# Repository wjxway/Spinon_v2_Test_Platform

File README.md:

# Maneuverable Piccolissimo 4 (MP4) Test Platform Setup Guide

Maneuverable Piccolissimo 4 test platform, or MP4 test platform for short, is a single motor drone system designed to test the dynamics of the drone before we build the full distributed version of MP4 system. Instead of using peer-to-peer communication between drones to achieve control like it will be in the MP4 system, this test platform uses external optical tracking system like Optitrack to obtain high accuracy drone position, making it easier to test subsystems like aerodynamics or control.

For more details of this system, please check (and cite!) our paper at [RSS proceedings website](https://www.roboticsproceedings.org/rss20/p102.html). For assembly guide, please visit [this document](https://1drv.ms/w/s!Aq5Al0CEiWQnkfE0qJTTQATZVnzniQ).

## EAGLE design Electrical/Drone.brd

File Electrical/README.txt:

CAM_Files.zip contains the CAM files needed to manufacture and assemble the PCB.

In the schematics, I'm using pinhead as power plugs and SSM6K504NU FET instead of the G2014.
When building the board, make sure you do not install the pinhead (use wires with headers instead) and install Goford G2014 FET.

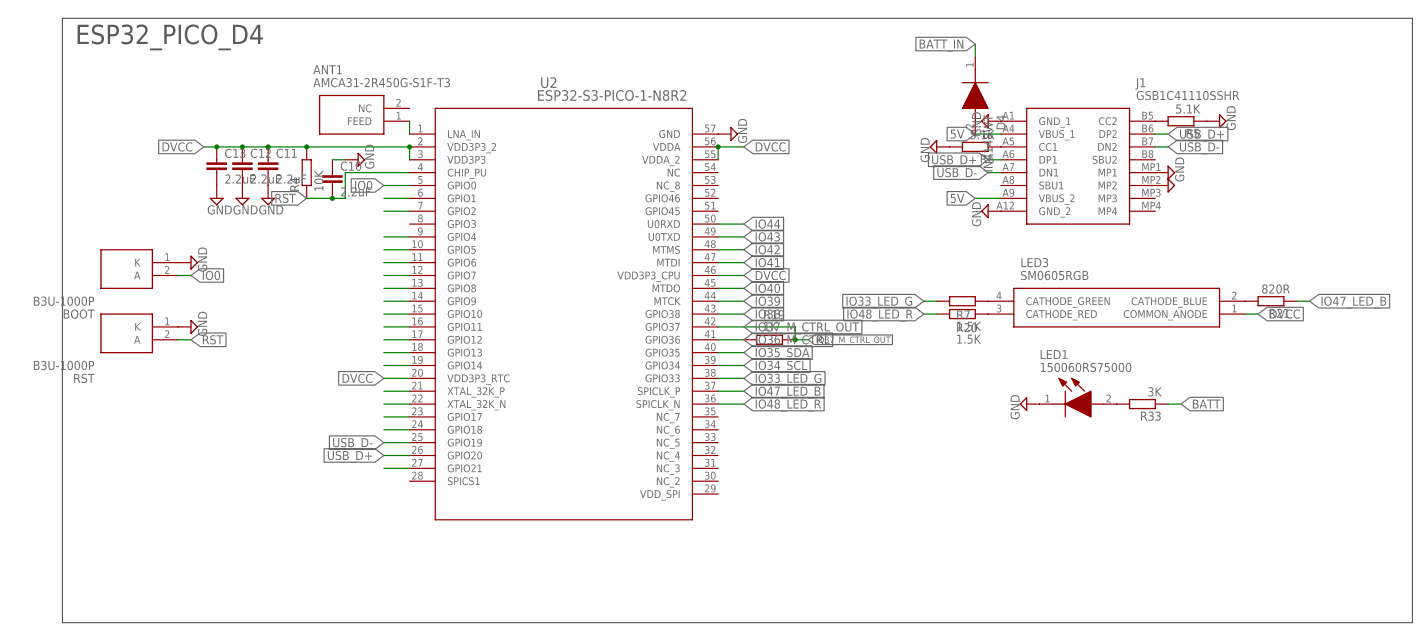
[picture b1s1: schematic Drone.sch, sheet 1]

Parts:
ANT1: AMCA31-2R450G-S1F-T3; ANTC3216X140N
BOOT: B3U-1000P
C10, C11, C12, C13: 2.2uF; C0402_STANDARD
D4: IN4148WT; SODFL1608X70N
J1: GSB1C41110SSHR
LED1: 150060RS75000; LEDC1608X80N
LED3: SM0605RGB
R4: 10K; R0402_STANDARD
R5, R6: 5.1K; R0402_STANDARD
R7, R20: 1.5K; R0402_STANDARD
R19: 1K; R0402_STANDARD
R21: 820R; R0402_STANDARD
R33: 3K; R0402_STANDARD
RST: B3U-1000P
U2: ESP32-S3-PICO-1-N8R2; QFN56_7X7_EXP

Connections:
5V: D4.2 (A), J1.A4 (VBUS_1), J1.A9 (VBUS_2)
BATT: R33.1; also elsewhere on the board
BATT_IN: D4.1 (K); also elsewhere on the board
DVCC: C11.1, C12.1, C13.1, LED3.1 (COMMON_ANODE), R4.2, U2.2 (VDD3P3_2), U2.3 (VDD3P3), U2.20 (VDD3P3_RTC), U2.46 (VDD3P3_CPU), U2.55 (VDDA_2), U2.56 (VDDA); also elsewhere on the board
GND: BOOT.1 (K), C10.1, C11.2, C12.2, C13.2, J1.A1 (GND_1), J1.A12 (GND_2), J1.MP1, J1.MP2, LED1.1 (K), R5.1, R6.2, RST.1 (K), U2.57 (GND); also elsewhere on the board
IO0: BOOT.2 (A), U2.5 (GPIO0)
IO33_LED_G: R7.2, U2.38 (GPIO33)
IO34_SCL: U2.39 (GPIO34); also elsewhere on the board
IO35_SDA: U2.40 (GPIO35); also elsewhere on the board
IO36_M_CTRL: R19.2, U2.41 (GPIO36)
IO37_M_CTRL_OUT: R19.1, U2.42 (GPIO37); also elsewhere on the board
IO38: U2.43 (GPIO38)
IO39: U2.44 (MTCK)
IO40: U2.45 (MTDO)
IO41: U2.47 (MTDI)
IO42: U2.48 (MTMS)
IO43: U2.49 (U0TXD)
IO44: U2.50 (U0RXD)
IO47_LED_B: R21.1, U2.37 (SPICLK_P)
IO48_LED_R: R20.2, U2.36 (SPICLK_N)
unnamed: ANT1.1 (FEED), U2.1 (LNA_IN)
unnamed: LED3.4 (CATHODE_GREEN), R7.1
unnamed: J1.A5 (CC1), R6.1
unnamed: LED1.2 (A), R33.2
unnamed: LED3.2 (CATHODE_BLUE), R21.2
unnamed: J1.B5 (CC2), R5.2
unnamed: LED3.3 (CATHODE_RED), R20.1
RST: C10.2, R4.1, RST.2 (A), U2.4 (CHIP_PU)
USB_D+: J1.A6 (DP1), J1.B6 (DP2), U2.26 (GPIO20)
USB_D-: J1.A7 (DN1), J1.B7 (DN2), U2.25 (GPIO19)
VDD_SPI: U2.29 (VDD_SPI)

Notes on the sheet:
ESP32_PICO_D4

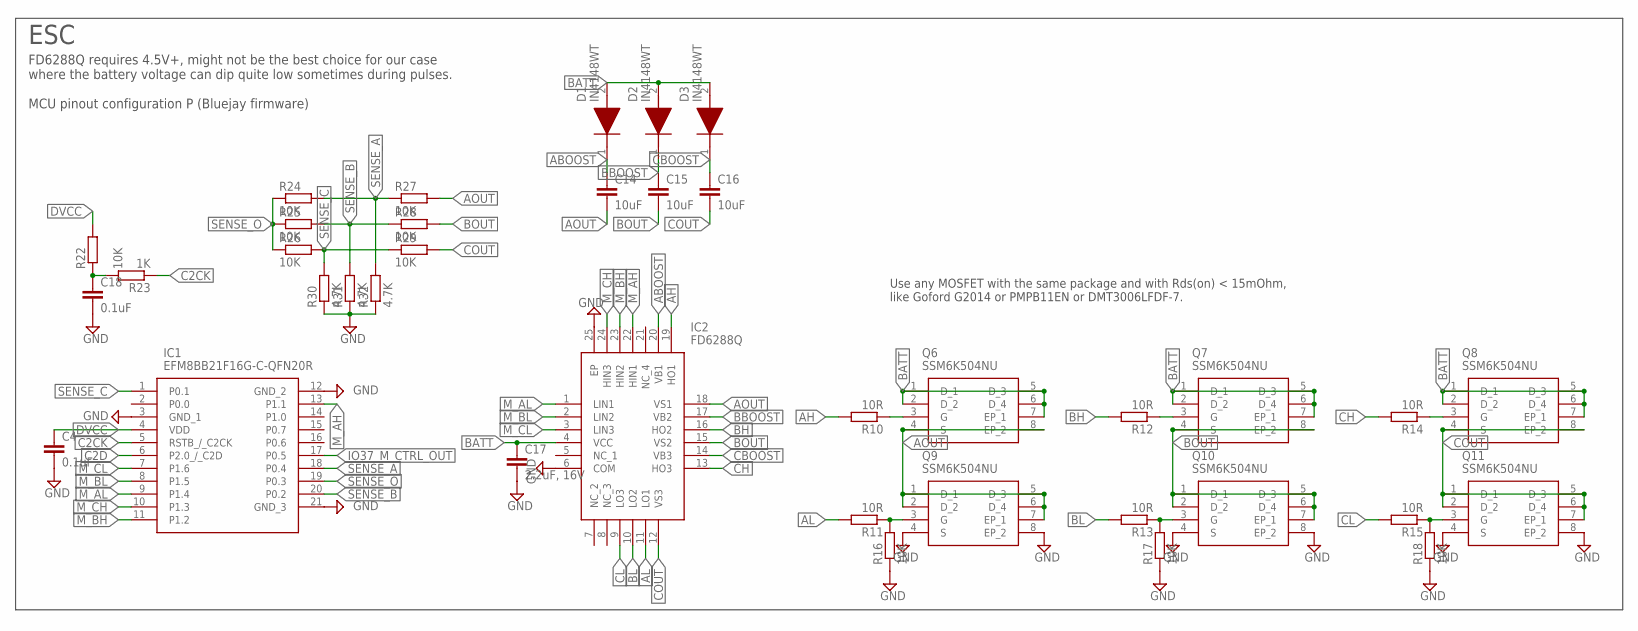
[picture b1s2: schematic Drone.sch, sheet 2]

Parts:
C4, C18: 0.1uF; C0402_STANDARD
C14, C15, C16: 10uF; C0402_STANDARD
C17: 2.2uF, 16V; C0402_STANDARD
D1, D2, D3: IN4148WT; SODFL1608X70N
IC1: EFM8BB21F16G-C-QFN20R; EFM8BB21F16GCQFN20R
IC2: FD6288Q; QFN50P400X400X90-25N
Q6, Q7, Q8, Q9, Q10, Q11: SSM6K504NU
R10, R11, R12, R13, R14, R15: 10R; R0402_STANDARD
R16, R17, R18, R22, R24, R25, R26, R27, R28, R29: 10K; R0402_STANDARD
R23: 1K; R0402_STANDARD
R30, R31, R32: 4.7K; R0402_STANDARD

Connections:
ABOOST: C14.1, D1.1 (K), IC2.20 (VB1)
AH: IC2.19 (HO1), R10.2
AL: IC2.11 (LO1), R11.2
AOUT: C14.2, IC2.18 (VS1), Q6.4 (S), Q6.8 (EP_2), Q9.1 (D_1), Q9.2 (D_2), Q9.5 (D_3), Q9.6 (D_4), Q9.7 (EP_1), R27.2
BATT: C17.1, D1.2 (A), D2.2 (A), D3.2 (A), IC2.4 (VCC), Q6.1 (D_1), Q6.2 (D_2), Q6.5 (D_3), Q6.6 (D_4), Q6.7 (EP_1), Q7.1 (D_1), Q7.2 (D_2), Q7.5 (D_3), Q7.6 (D_4), Q7.7 (EP_1), Q8.1 (D_1), Q8.2 (D_2), Q8.5 (D_3), Q8.6 (D_4), Q8.7 (EP_1); also elsewhere on the board
BBOOST: C15.1, D2.1 (K), IC2.17 (VB2)
BH: IC2.16 (HO2), R12.2
BL: IC2.10 (LO2), R13.2
BOUT: C15.2, IC2.15 (VS2), Q7.4 (S), Q7.8 (EP_2), Q10.1 (D_1), Q10.2 (D_2), Q10.5 (D_3), Q10.6 (D_4), Q10.7 (EP_1), R28.2
C2CK: IC1.5 (RSTB_/_C2CK), R23.1
C2D: IC1.6 (P2.0_/_C2D)
CBOOST: C16.1, D3.1 (K), IC2.14 (VB3)
CH: IC2.13 (HO3), R14.2
CL: IC2.9 (LO3), R15.2
COUT: C16.2, IC2.12 (VS3), Q8.4 (S), Q8.8 (EP_2), Q11.1 (D_1), Q11.2 (D_2), Q11.5 (D_3), Q11.6 (D_4), Q11.7 (EP_1), R29.2
DVCC: C4.1, IC1.4 (VDD), R22.2; also elsewhere on the board
GND: C4.2, C17.2, C18.2, IC1.3 (GND_1), IC1.12 (GND_2), IC1.21 (GND_3), IC2.6 (COM), IC2.25 (EP), Q9.4 (S), Q9.8 (EP_2), Q10.4 (S), Q10.8 (EP_2), Q11.4 (S), Q11.8 (EP_2), R16.1, R17.1, R18.1, R30.1, R31.1, R32.1; also elsewhere on the board
IO37_M_CTRL_OUT: IC1.17 (P0.5); also elsewhere on the board
M_AH: IC1.13 (P1.1), IC2.22 (HIN1)
M_AL: IC1.9 (P1.4), IC2.1 (LIN1)
M_BH: IC1.11 (P1.2), IC2.23 (HIN2)
M_BL: IC1.8 (P1.5), IC2.2 (LIN2)
M_CH: IC1.10 (P1.3), IC2.24 (HIN3)
M_CL: IC1.7 (P1.6), IC2.3 (LIN3)
unnamed: Q6.3 (G), R10.1
unnamed: Q9.3 (G), R11.1, R16.2
unnamed: Q7.3 (G), R12.1
unnamed: Q10.3 (G), R13.1, R17.2
unnamed: Q8.3 (G), R14.1
unnamed: Q11.3 (G), R15.1, R18.2
unnamed: C18.1, R22.1, R23.2
SENSE_A: IC1.18 (P0.4), R24.2, R27.1, R32.2
SENSE_B: IC1.20 (P0.2), R25.2, R28.1, R31.2
SENSE_C: IC1.1 (P0.1), R26.2, R29.1, R30.2
SENSE_O: IC1.19 (P0.3), R24.1, R25.1, R26.1

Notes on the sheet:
ESC
FD6288Q requires 4.5V+, might not be the best choice for our case where the battery voltage can dip quite low sometimes during pulses. MCU pinout configuration P (Bluejay firmware)
Use any MOSFET with the same package and with Rds(on) < 15mOhm, like Goford G2014 or PMPB11EN or DMT3006LFDF-7.

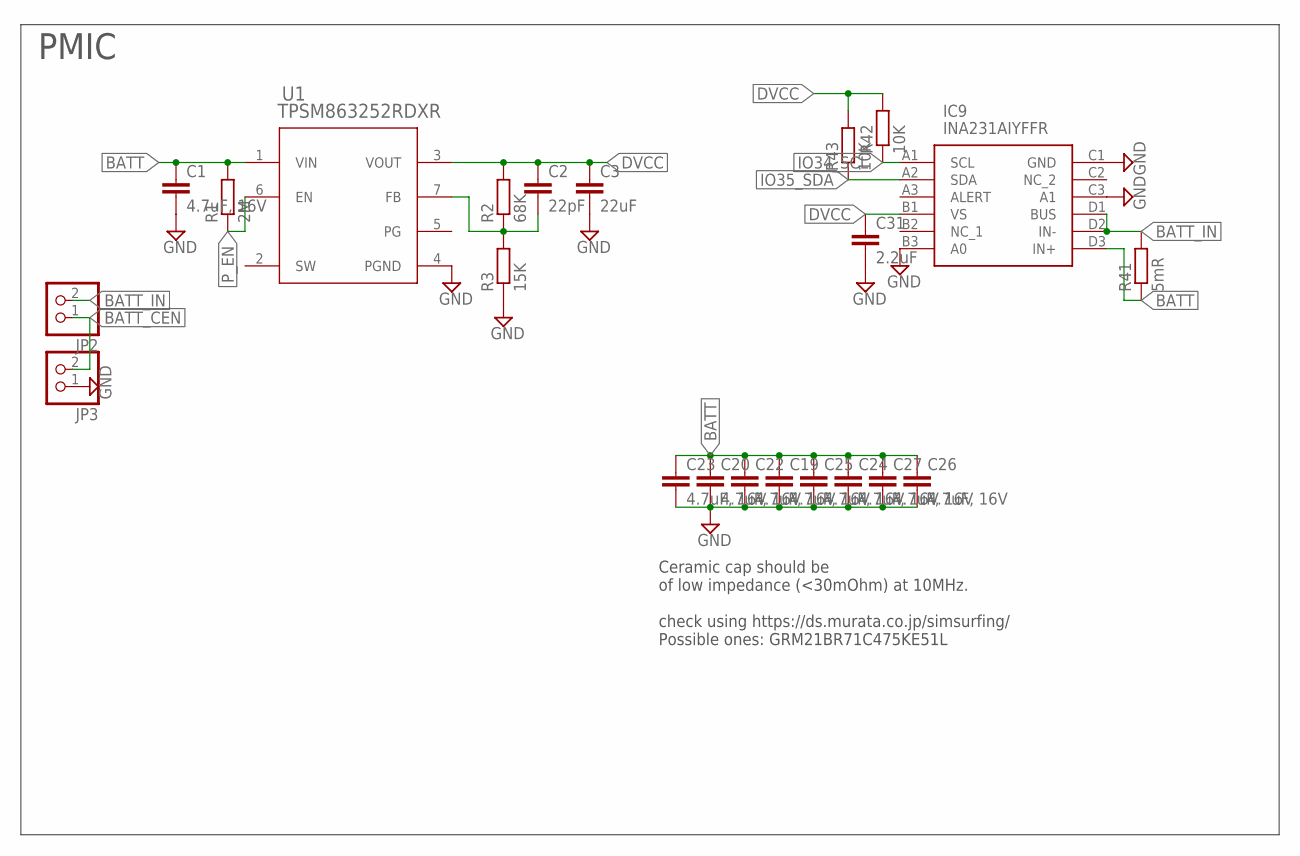
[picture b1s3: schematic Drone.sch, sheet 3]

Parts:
C1: 4.7uF, 16V; C0603
C2: 22pF; C0402_STANDARD
C3: 22uF; C0603
C19, C20, C22, C23, C24, C25, C26, C27: 4.7uF, 16V; C0805
C31: 2.2uF; C0402_STANDARD
IC9: INA231AIYFFR; BGA12C40P3X4_139X164X62
JP2, JP3: PINHD-1X2; 1X02
R1: 2M; R0402_STANDARD
R2: 68K; R0402_STANDARD
R3: 15K; R0402_STANDARD
R41: 5mR; R0805
R42, R43: 10K; R0402_STANDARD
U1: TPSM863252RDXR; RDX0007A-MFG

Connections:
BATT: C1.1, C19.1, C20.1, C22.1, C23.1, C24.1, C25.1, C26.1, C27.1, IC9.D3 (IN+), R1.2, R41.1, U1.1 (VIN); also elsewhere on the board
BATT_CEN: JP2.1, JP3.2
BATT_IN: IC9.D1 (BUS), IC9.D2 (IN-), JP2.2, R41.2; also elsewhere on the board
DVCC: C2.1, C3.1, C31.1, IC9.B1 (VS), R2.2, R42.2, R43.2, U1.3 (VOUT); also elsewhere on the board
GND: C1.2, C3.2, C19.2, C20.2, C22.2, C23.2, C24.2, C25.2, C26.2, C27.2, C31.2, IC9.B3 (A0), IC9.C1 (GND), IC9.C3 (A1), JP3.1, R3.1, U1.4 (PGND); also elsewhere on the board
IO34_SCL: IC9.A1 (SCL), R42.1; also elsewhere on the board
IO35_SDA: IC9.A2 (SDA), R43.1; also elsewhere on the board
unnamed: C2.2, R2.1, R3.2, U1.7 (FB)
P_EN: R1.1, U1.6 (EN)

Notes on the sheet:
PMIC
Ceramic cap should be of low impedance (<30mOhm) at 10MHz. check using https://ds.murata.co.jp/simsurfing/ Possible ones: GRM21BR71C475KE51L

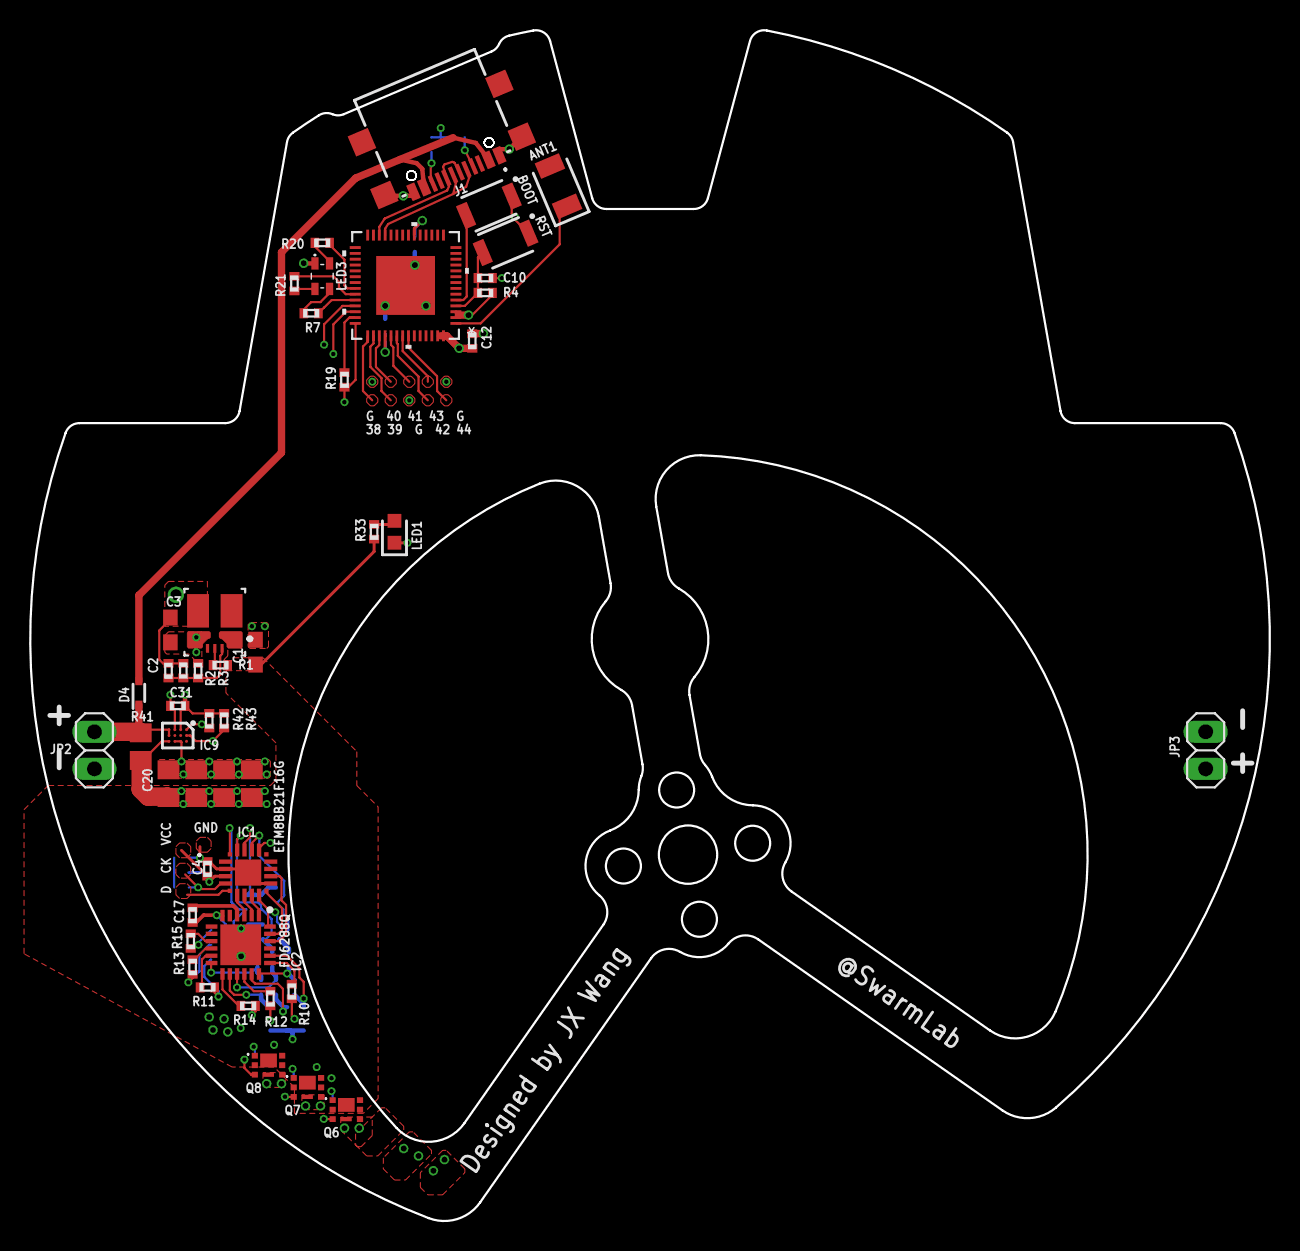
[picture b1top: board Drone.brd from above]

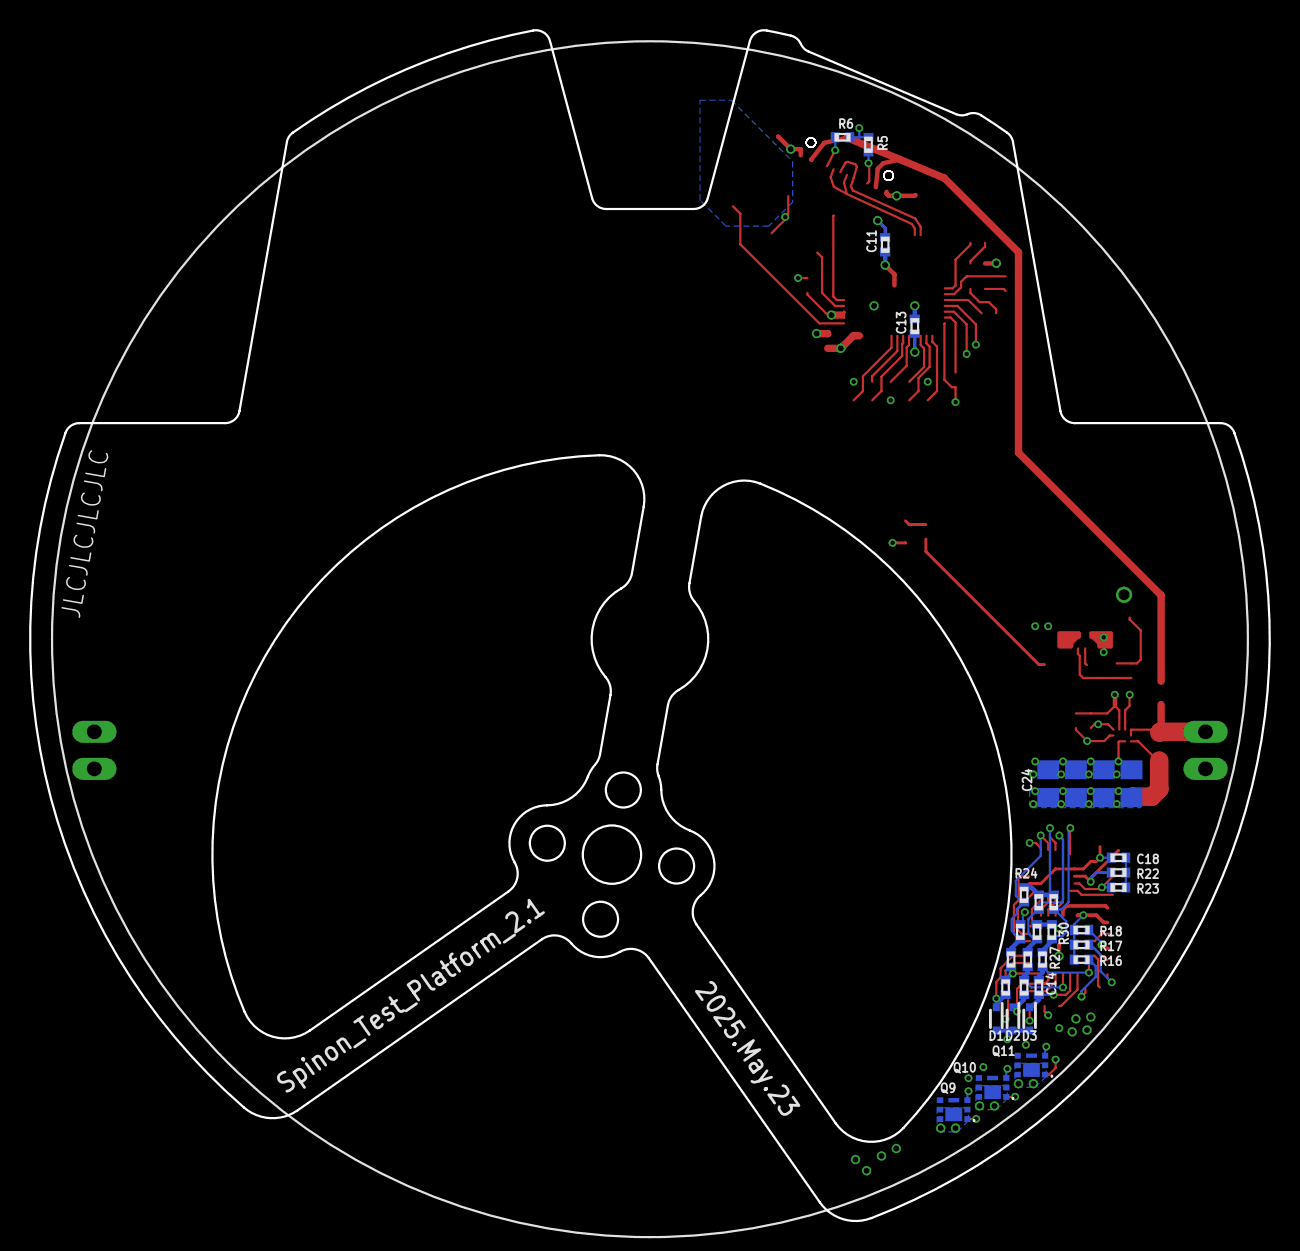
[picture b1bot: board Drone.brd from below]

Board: 4 copper layers, 85.0 x 81.6 mm, 79 parts (32 on the bottom side), 56 nets.

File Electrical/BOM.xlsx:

Qty | Value | Device | Package | Parts | Description | ARROW_PART_NUMBER | ARROW_PRICE-STOCK | COPYRIGHT | DESCRIPTION.1 | HEIGHT | MANUFACTURER_NAME | MANUFACTURER_PART_NUMBER | MFR_NAME | MOUSER_PART_NUMBER | MOUSER_PRICE-STOCK | MOUSER_TESTING_PART_NUMBER | MOUSER_TESTING_PRICE-STOCK | POPULARITY | REFDES | SPICEPREFIX | TYPE | Column1
2 |  | PINHD-1X2 | 1X02 | JP2, JP3 | PIN HEADER |  |  |  |  |  |  |  |  |  |  |  |  | 98
2 | 0.1uF | C0402_STANDARD | C0402_STANDARD | C4, C18
2 | 1.5K | R0402_STANDARD | R0402_STANDARD | R7, R20
13 | 10K | R0402_STANDARD | R0402_STANDARD | R4, R16, R17, R18, R22, R24, R25, R26, R27, R28, R29, R42, R43
6 | 10R | R0402_STANDARD | R0402_STANDARD | R10, R11, R12, R13, R14, R15
3 | 10uF | C0402_STANDARD | C0402_STANDARD | C14, C15, C16
1 | 150060RS75000 | 150060RS75000 | LEDC1608X80N | LED1 | WURTH ELEKTRONIK - 150060RS75000 - LED, 0603, RED, 250MCD, 625NM |  |  |  | WURTH ELEKTRONIK - 150060RS75000 - LED, 0603, RED, 250MCD, 625NM | 0.8mm | Wurth Elektronik | 150060RS75000 |  | 710-150060RS75000 | https://www.mouser.co.uk/ProductDetail/Wurth-Elektronik/1500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
1 | 15K | R0402_STANDARD | R0402_STANDARD | R3
2 | 1K | R0402_STANDARD | R0402_STANDARD | R19, R23
5 | 2.2uF | C0402_STANDARD | C0402_STANDARD | C10, C11, C12, C13, C31
1 | 2.2uF, 16V | C0402_STANDARD | C0402_STANDARD | C17
1 | 22pF | C0402_STANDARD | C0402_STANDARD | C2
1 | 22uF | C-EUC0603 | C0603 | C3 | CAPACITOR, European symbol |  |  |  |  |  |  |  |  |  |  |  |  | 73 |  | C
1 | 2M | R0402_STANDARD | R0402_STANDARD | R1
1 | 3K | R0402_STANDARD | R0402_STANDARD | R33
3 | 4.7K | R0402_STANDARD | R0402_STANDARD | R30, R31, R32
1 | 4.7uF, 16V | C-EUC0603 | C0603 | C1 | CAPACITOR, European symbol |  |  |  |  |  |  |  |  |  |  |  |  | 73 |  | C
8 | 4.7uF, 16V | C-EUC0805 | C0805 | C19, C20, C22, C23, C24, C25, C26, C27 | CAPACITOR, European symbol |  |  |  |  |  |  |  |  |  |  |  |  | 88 |  | C
2 | 5.1K | R0402_STANDARD | R0402_STANDARD | R5, R6
1 | 5mR | R-EU_R0805 | R0805 | R41 | RESISTOR, European symbol |  |  |  |  |  |  |  |  |  |  |  |  | 86 |  | R
1 | 68K | R0402_STANDARD | R0402_STANDARD | R2
1 | 820R | R0402_STANDARD | R0402_STANDARD | R21
1 | AMCA31-2R450G-S1F-T3 | AMCA31-2R450G-S1F-T3 | ANTC3216X140N | ANT1 | ABRACON - AMCA31-2R450G-S1F-T3 - ANTENNA, CHIP, 2.45GHZ, 50 OHM, 1206 | AMCA31-2R450G-S1F-T3 | https://www.arrow.com/en/products/amca31-2r450g-s1f-t3/abrac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 |  | ABRACON - AMCA31-2R450G-S1F-T3 - ANTENNA, CHIP, 2.45GHZ, 50 OHM, 1206 | 1.4mm | ABRACON | AMCA31-2R450G-S1F-T3 |  | 815-CA312R450GS1FT3 | https://www.mouser.co.uk/ProductDetail/ABRACON/AMCA31-2R450G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
2 | B3U-1000P | B3U-1000P | B3U-1000P | BOOT, RST | OMRON ELECTRONIC COMPONENTS - B3U-1000P - SWITCH, SPST-NO, 0.05A, 12V, SMD | B3U-1000P | https://www.arrow.com/en/products/b3u1000p/omron?region=europe |  | OMRON ELECTRONIC COMPONENTS - B3U-1000P - SWITCH, SPST-NO, 0.05A, 12V, SMD | mm | Omron Electronics | B3U-1000P |  | 653-B3U-1000P | https://www.mouser.co.uk/ProductDetail/Omron-Electronics/B3U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
1 | EFM8BB21F16G-C-QFN20R | EFM8BB21F16G-C-QFN20R | EFM8BB21F16GCQFN20R | IC1 | SILICON LABS - EFM8BB21F16G-C-QFN20R - 8 Bit MCU, EFM8 Family EFM8BB Series Mic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 | EFM8BB21F16G-C-QFN20R | https://www.arrow.com/en/products/efm8bb21f16g-c-qfn20r/sili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 |  | SILICON LABS - EFM8BB21F16G-C-QFN20R - 8 Bit MCU, EFM8 Family EFM8BB Series Mic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 | 0.8mm | Silicon Labs | EFM8BB21F16G-C-QFN20R |  | 634-8BB21F16GCQFN20R | https://www.mouser.co.uk/ProductDetail/Silicon-Labs/EFM8BB21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
1 | ESP32-S3-PICO-1-N8R2 | ESP32-S3-PICO-1-N8R2 | QFN56_7X7_EXP | U2 |  |  |  | Copyright (C) 2024 Ultra Librarian. All rights reserved. |  |  |  | ESP32-S3-PICO-1-N8R2 | Espressif Systems
1 | FD6288Q | FD6288Q | QFN50P400X400X90-25N | IC2 | QFN-24 MOS Drivers RoHS |  |  |  | QFN-24 MOS Drivers RoHS | 0.9mm | Fortior Tech | FD6288Q
1 | GSB1C41110SSHR | GSB1C41110SSHR | GSB1C41110SSHR | J1 | USB2.0, Type C, Top mount, Center Height 1.63mm, Single Row Surface Mount |  |  |  | USB2.0, Type C, Top mount, Center Height 1.63mm, Single Row Surface Mount | 3.41mm | Amphenol Communications Solutions | GSB1C41110SSHR
4 | IN4148WT | IN4148WT | SODFL1608X70N | D1, D2, D3, D4 | SMD Small Signal Switching Diode |  |  |  | SMD Small Signal Switching Diode | 0.7mm | Diotec | IN4148WT
1 | INA231AIYFFR | INA231AIYFFR | BGA12C40P3X4_139X164X62 | IC9 | 28V, Bi-Directional, Low-/High-Side, I2C Out Current/Power Monitor w/Alert in W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 | INA231AIYFFR | https://www.arrow.com/en/products/ina231aiyffr/texas-instrum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 |  | 28V, Bi-Directional, Low-/High-Side, I2C Out Current/Power Monitor w/Alert in W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 | 0.625mm | Texas Instruments | INA231AIYFFR |  | 595-INA231AIYFFR | https://www.mouser.co.uk/ProductDetail/Texas-Instruments/INA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
1 | SM0605RGB | SM0605RGB | SM0605RGB | LED3 | SM0605RGB, Bivar 470 nm, 525 nm, 635 nm 3 RGB LED, 4-Pin 0605 Clear SMD package | SM0605RGB | https://www.arrow.com/en/products/sm0605rgb/bivar?region=nac |  | SM0605RGB, Bivar 470 nm, 525 nm, 635 nm 3 RGB LED, 4-Pin 0605 Clear SMD package | 0.6mm | Bivar | SM0605RGB |  | 749-SM0605TCRGB | https://www.mouser.co.uk/ProductDetail/Bivar/SM0605RGB?qs=pf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
6 | SSM6K504NU | SSM6K504NU | SSM6K504NU | Q6, Q7, Q8, Q9, Q10, Q11 | Small Low ON resistance MOSFETs |  |  |  | Small Low ON resistance MOSFETs | 0.8mm | Toshiba | SSM6K504NU |  | N/A | https://www.mouser.co.uk/ProductDetail/Toshiba/SSM6K504NU?qs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
1 | TPSM863252RDXR | TPSM863252RDXR | RDX0007A-MFG | U1 |  |  |  | Copyright (C) 2024 Ultra Librarian. All rights reserved. |  |  |  | TPSM863252RDXR | Texas Instruments |  |  |  |  |  | RefDes |  | TYPE

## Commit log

2025-01-22 Simplify PCB design
2025-06-02 v2.1

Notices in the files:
parts and their libraries:
COPYRIGHT: Copyright (C) 2024 Ultra Librarian. All rights reserved.
